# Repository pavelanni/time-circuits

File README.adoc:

= The Time Circuits

This is my implementation of the link:https://backtothefuture.fandom.com/wiki/Time_circuits[time circuits] invented by Doc Brown.
The main controllers used here are Raspberry Pi Pico.
The code is written in Go and compiled for Pico using TinyGo.

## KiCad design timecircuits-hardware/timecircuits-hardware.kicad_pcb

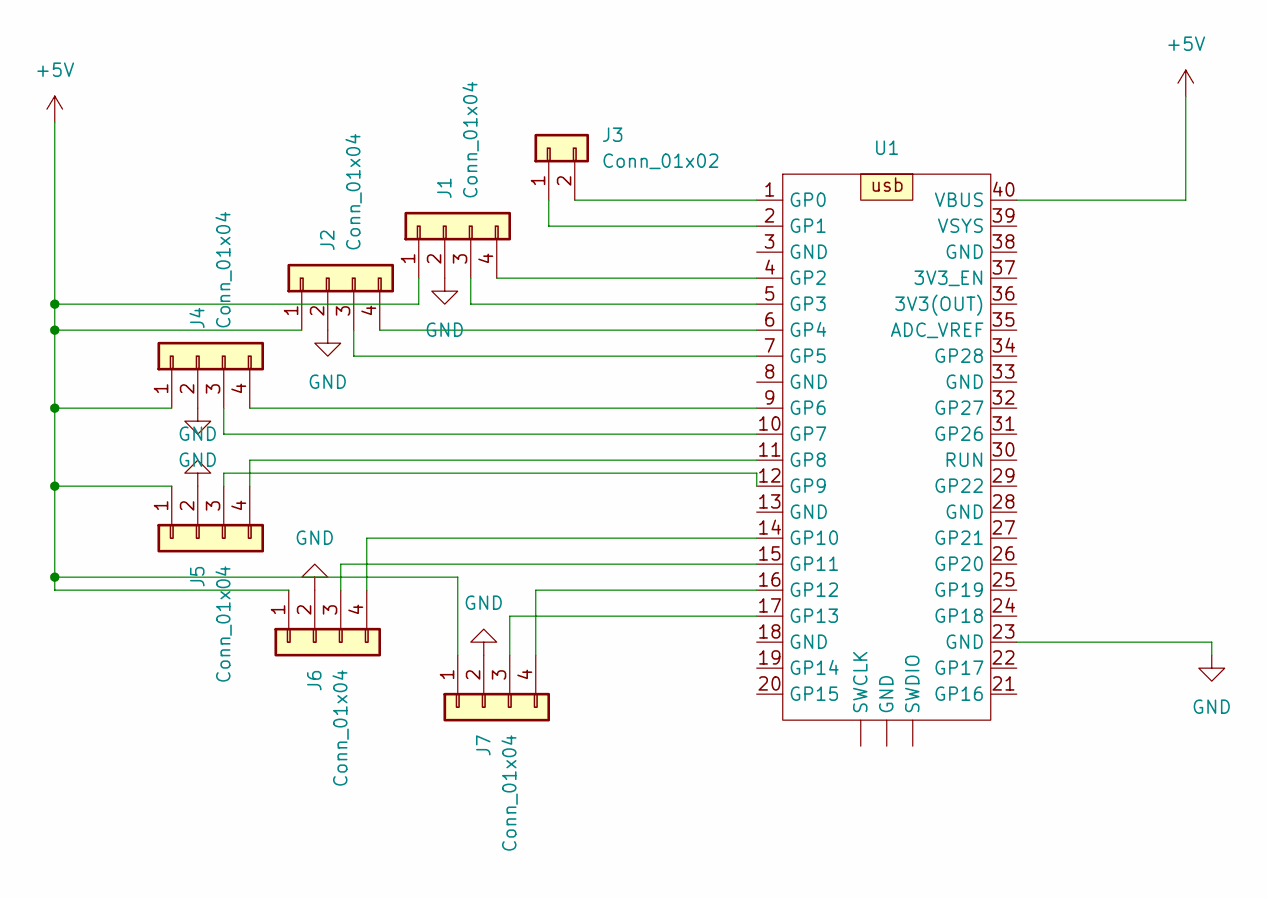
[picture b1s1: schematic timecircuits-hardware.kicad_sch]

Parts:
J1, J2, J4, J5, J6, J7: Conn_01x04; PinHeader_1x04_P2.54mm_Vertical
J3: Conn_01x02; PinHeader_1x02_P2.54mm_Vertical
U1: Raspberry_pi_pico

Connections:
+5V: J1.1, J2.1, J4.1, J5.1, J6.1, J7.1, U1.40 (VBUS)
GND: J1.2, J2.2, J4.2, J5.2, J6.2, J7.2, U1.23 (GND)
unnamed: J1.3, U1.5 (GP3)
unnamed: J1.4, U1.4 (GP2)
unnamed: J2.3, U1.7 (GP5)
unnamed: J2.4, U1.6 (GP4)
unnamed: J3.1, U1.2 (GP1)
unnamed: J3.2, U1.1 (GP0)
unnamed: J4.3, U1.10 (GP7)
unnamed: J4.4, U1.9 (GP6)
unnamed: J5.3, U1.12 (GP9)
unnamed: J5.4, U1.11 (GP8)
unnamed: J6.3, U1.15 (GP11)
unnamed: J6.4, U1.14 (GP10)
unnamed: J7.3, U1.17 (GP13)
unnamed: J7.4, U1.16 (GP12)

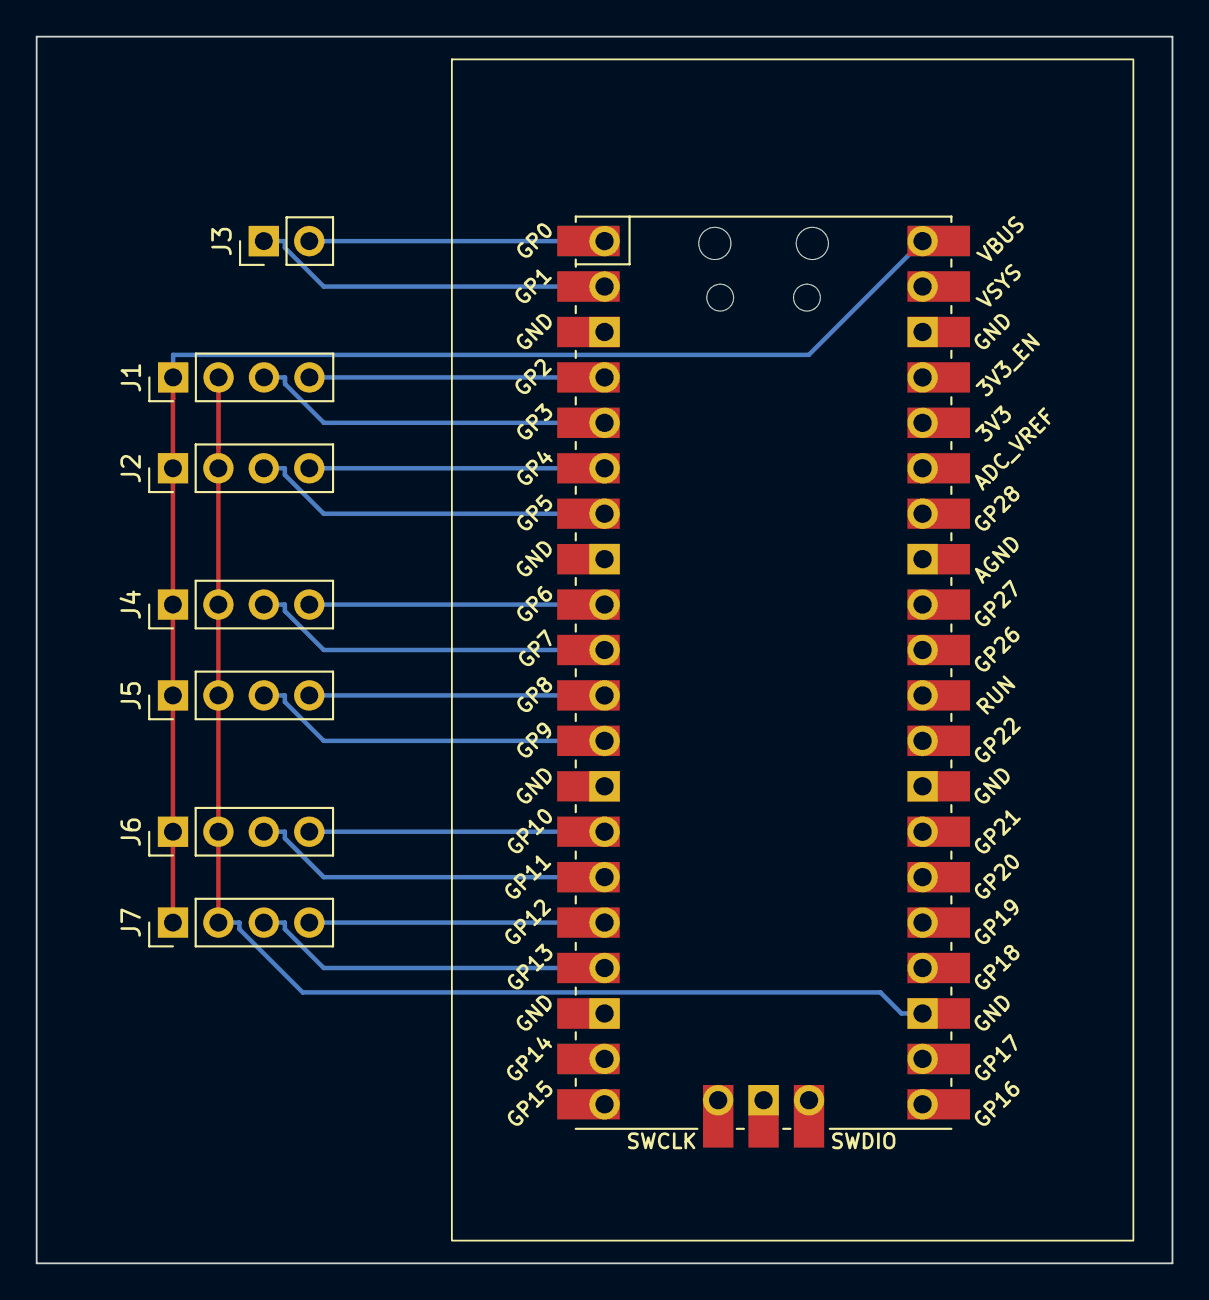
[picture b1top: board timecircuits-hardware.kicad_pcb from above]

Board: 2 copper layers, 63.5 x 68.6 mm, 8 parts (0 on the bottom side), 16 nets.

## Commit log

2023-09-10 add actual pins to setyear
2023-09-13 add second Pico for present and last departed
2023-09-16 change to RFC3339
2023-09-28 add KiCAD hardware dir; change to max brightness
2023-09-30 before removing RTC and switching to flash
2023-09-30 save dates in flash (present and destination)
2023-09-30 minor: remove ln from print
2023-09-30 minor: output cleanup
2023-10-01 one-off error
2023-10-15 add sound effects
2023-10-21 change UART speed to 9600
2023-10-22 add button debounce
2023-10-22 set stopbits to 2, parity to 0
2023-10-30 add STX and ETX to the message
